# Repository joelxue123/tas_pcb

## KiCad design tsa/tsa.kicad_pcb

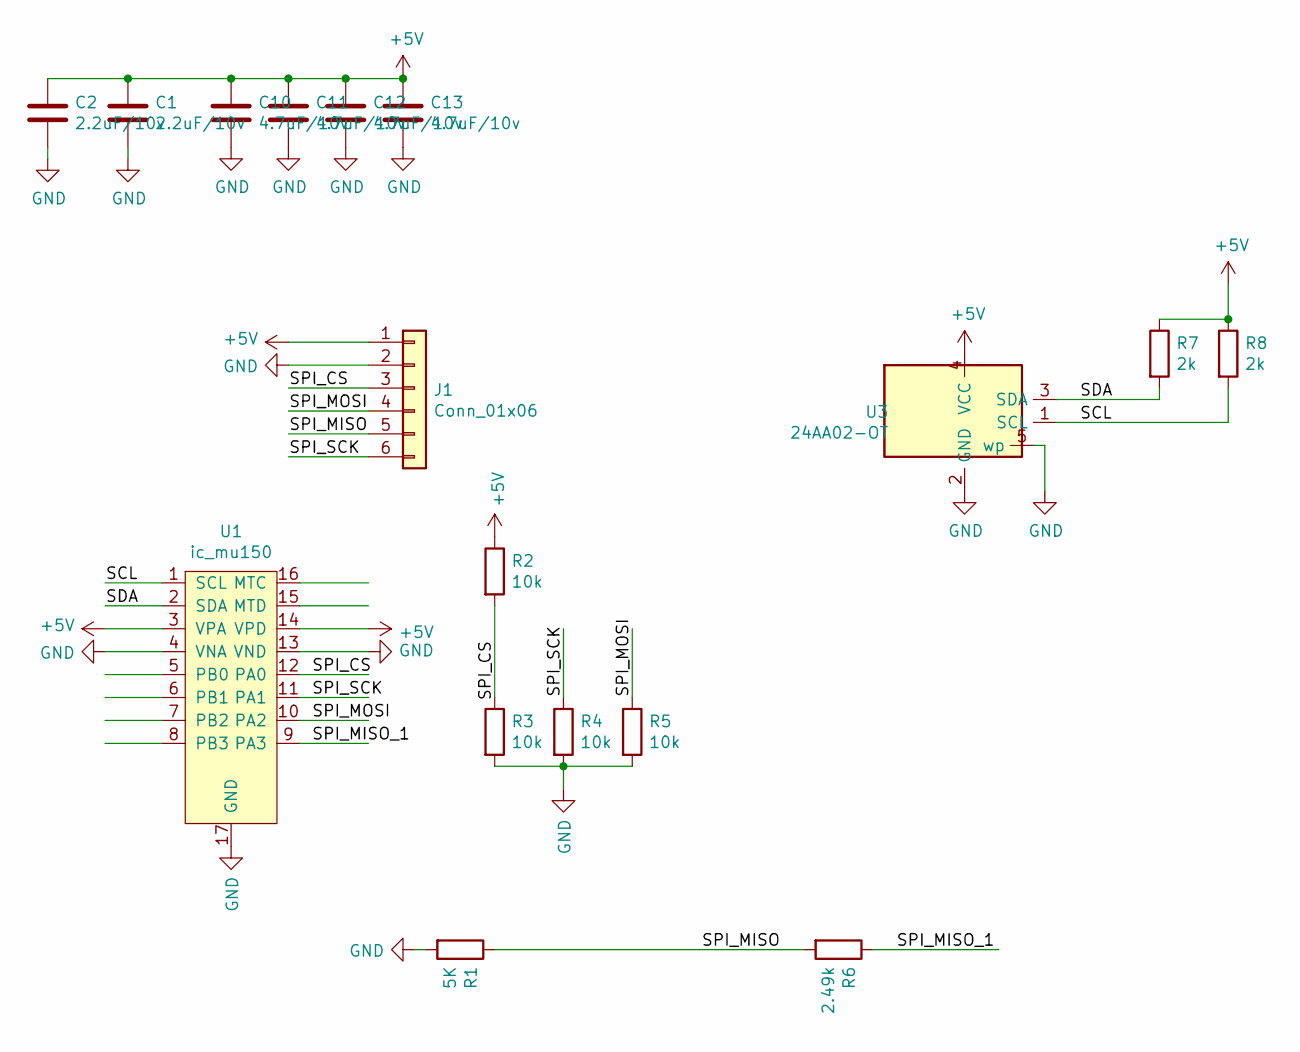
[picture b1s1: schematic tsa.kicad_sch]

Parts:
C1, C2: 2.2uF/10v; C_0201_0603Metric
C10, C11, C12, C13: 4.7uF/10v; C_0402_1005Metric
J1: Conn_01x06; PinSocket_1x06_P1.27mm_Vertical
R1: 5K; R_0402_1005Metric
R2, R3, R4, R5: 10k; R_0402_1005Metric
R6: 2.49k; R_0402_1005Metric
R7, R8: 2k; R_0402_1005Metric
U1: ic_mu150; DFN-16-1EP_5x5mm_P0.5mm_EP3.46x4mm
U3: 24AA02-OT; SOT-23-5

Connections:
+5V: C1.1, C2.1, C10.1, C11.1, C12.1, C13.1, J1.1, R2.1, R7.1, R8.1, U1.3 (VPA), U1.14 (VPD), U3.4 (VCC)
/SCL: R8.2, U1.1 (SCL), U3.1 (SCL)
/SDA: R7.2, U1.2 (SDA), U3.3 (SDA)
/SPI_CS: J1.3, R2.2, R3.1, U1.12 (PA0)
/SPI_MISO: J1.5, R1.1, R6.2
/SPI_MISO_1: R6.1, U1.9 (PA3)
/SPI_MOSI: J1.4, R5.1, U1.10 (PA2)
/SPI_SCK: J1.6, R4.1, U1.11 (PA1)
GND: C1.2, C2.2, C10.2, C11.2, C12.2, C13.2, J1.2, R1.2, R3.2, R4.2, R5.2, U1.4 (VNA), U1.13 (VND), U1.17 (GND), U3.2 (GND), U3.5 (wp)

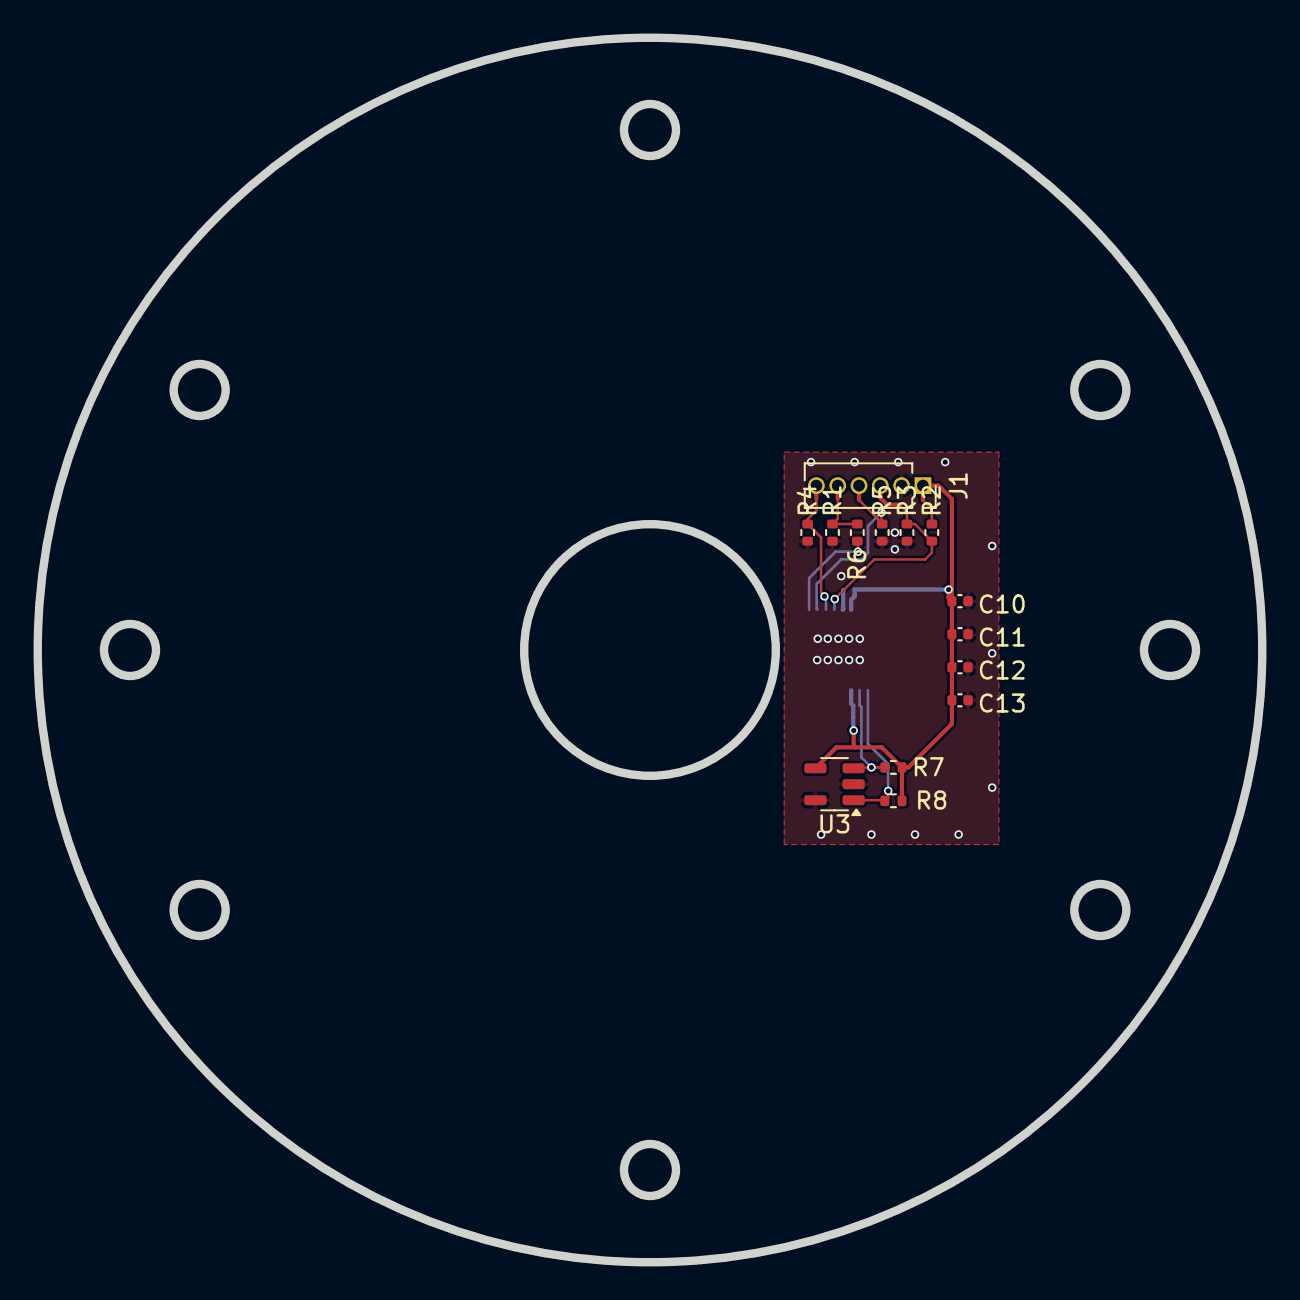
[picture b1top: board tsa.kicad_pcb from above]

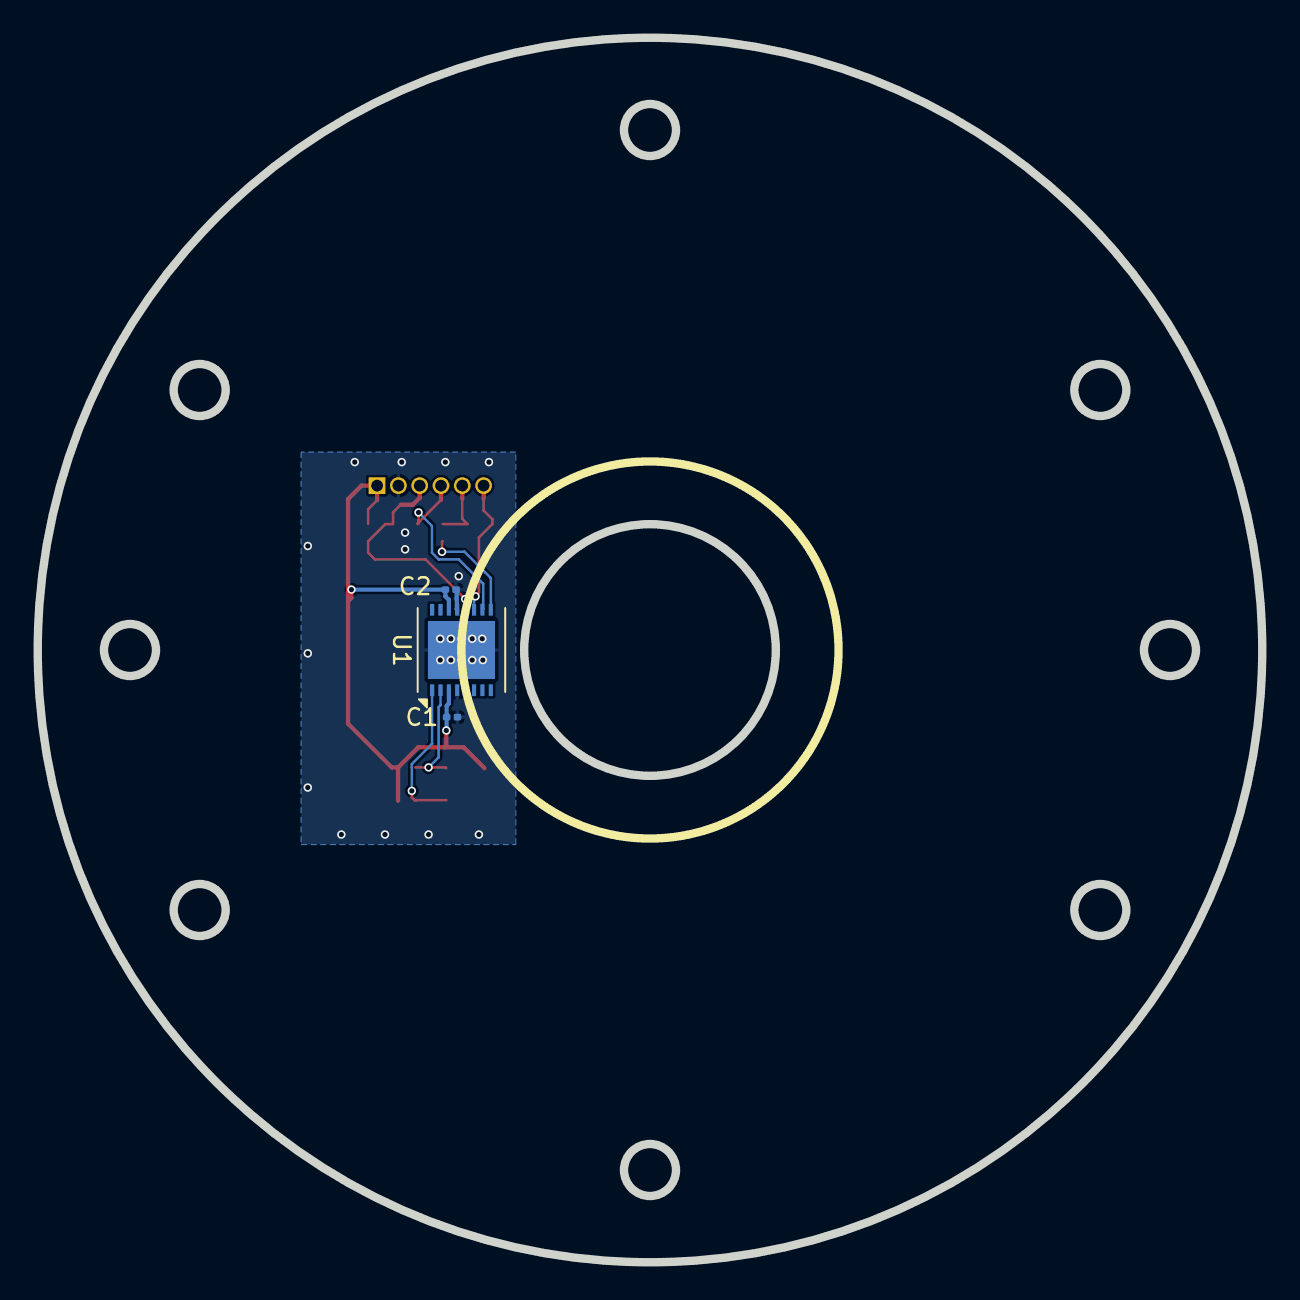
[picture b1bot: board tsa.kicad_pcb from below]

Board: 2 copper layers, 73.0 x 73.0 mm, 17 parts (3 on the bottom side), 9 nets.

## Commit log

2024-05-10 tsa pcb -first
